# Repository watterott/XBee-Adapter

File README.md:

# XBee-Adapter
The XBee-Adapter is an USB to serial adapter and breakout for XBee modules.

* [FTDI FT231X](https://www.ftdichip.com/Products/ICs/FT231X.html) USB UART Bridge
* 3.3V 0.8A LDO voltage regulator
* Status LEDs
* All pins available on 2.54mm headers
* microUSB-Connector
* Open-Source and released under the [Creative Commons Attribution Share-Alike License](https://creativecommons.org/licenses/by-sa/4.0/).
* **[Documentation on learn.watterott.com](https://learn.watterott.com)**

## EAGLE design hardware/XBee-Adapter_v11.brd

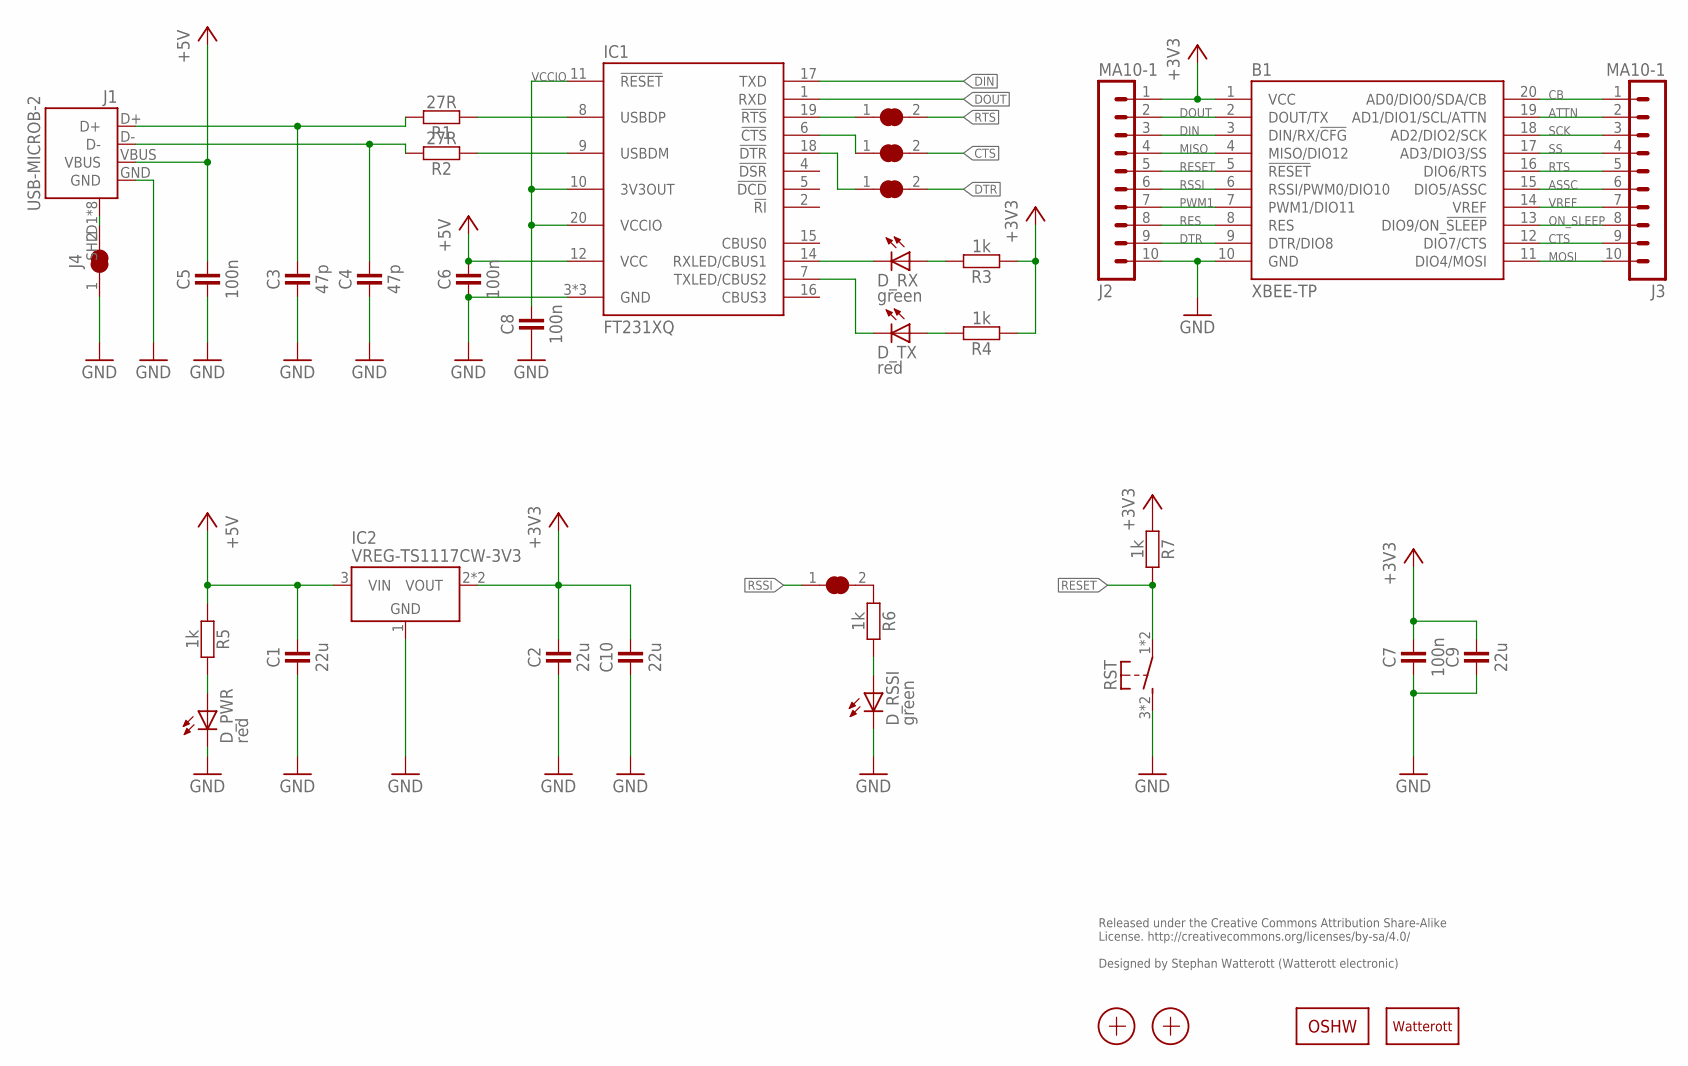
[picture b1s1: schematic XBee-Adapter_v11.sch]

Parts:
B1: XBEE-TP; XBEE_TP
C1, C2, C9, C10: 22u; C0805
C3, C4: 47p; C0402
C5, C6, C7, C8: 100n; C0402
CTS: JUMPER2-0603
DTR: JUMPER2-0603
D_PWR: red; C0603
D_RSSI: green; C0603
D_RX: green; C0603
D_TX: red; C0603
IC1: FT231XQ; QFN20-PAD
IC2: VREG-TS1117CW-3V3; SOT223
J1: USB-MICROB-2; USB-MICROB-10118194
J2, J3: MA10-1
J4: JUMPER2-0603
LOGO1: OSHW_LOGOX0150; OSHW_6X150
LOGO2: LOGO-S_PLACE_M; SPARK_TPLACE_M
R1, R2: 27R; C0603
R3, R4, R5, R6, R7: 1k; C0402
RSSI: JUMPER2-0603
RST: SW-TACTILE-PTS840P; PTS840P
RTS: JUMPER2-0603
X1, X2: PASSER-07; PASSER_07MM

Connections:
+3V3: B1.1 (VCC), C2.2, C7.2, C9.2, C10.2, IC2.2 (VOUT), IC2.4 (VOUT), J2.1, R3.1, R4.1, R7.1
+5V: C1.2, C5.2, C6.2, IC1.12 (VCC), IC2.3 (VIN), J1.VBUS, R5.1
ASSC: B1.15 (DIO5/ASSC), J3.6
ATTN: B1.19 (AD1/DIO1/SCL/ATTN), J3.2
CB: B1.20 (AD0/DIO0/SDA/CB), J3.1
CTS: B1.12 (DIO7/CTS), CTS.2, J3.9
DIN: B1.3 (DIN/RX/!CFG!), IC1.17 (TXD), J2.3
DOUT: B1.2 (DOUT/TX), IC1.1 (RXD), J2.2
DTR: B1.9 (DTR/DIO8), DTR.2, J2.9
D_N: C4.2, J1.D-, R2.2
D_P: C3.2, J1.D+, R1.2
GND: B1.10 (GND), C1.1, C2.1, C3.1, C4.1, C5.1, C6.1, C7.1, C8.1, C9.1, C10.1, D_PWR.C, D_RSSI.C, IC1.3 (GND), IC1.13 (GND), IC1.TP (GND), IC2.1 (GND), J1.GND, J2.10, J4.1, RST.3 (S1), RST.4 (S1)
MISO: B1.4 (MISO/DIO12), J2.4
MOSI: B1.11 (DIO4/MOSI), J3.10
unnamed: D_PWR.A, R5.2
unnamed: D_RSSI.A, R6.2
unnamed: R6.1, RSSI.2
unnamed: J1.SHLD1 (SHIELD), J1.SHLD2 (SHIELD), J1.SHLD3 (SHIELD), J1.SHLD4 (SHIELD), J1.SHLD5 (SHIELD), J1.SHLD6 (SHIELD), J1.SHLD7 (SHIELD), J1.SHLD8 (SHIELD), J4.2
unnamed: IC1.19 (!RTS), RTS.1
unnamed: CTS.1, IC1.6 (!CTS)
unnamed: D_RX.C, IC1.14 (RXLED/CBUS1)
unnamed: D_TX.C, IC1.7 (TXLED/CBUS2)
unnamed: D_RX.A, R3.2
unnamed: D_TX.A, R4.2
unnamed: DTR.1, IC1.18 (!DTR)
ON_SLEEP: B1.13 (DIO9/ON_!SLEEP!), J3.8
PWM1: B1.7 (PWM1/DIO11), J2.7
RES: B1.8 (RES), J2.8
RESET: B1.5 (!RESET!), J2.5, R7.2, RST.1, RST.2 (P1)
RSSI: B1.6 (RSSI/PWM0/DIO10), J2.6, RSSI.1
RTS: B1.16 (DIO6/RTS), J3.5, RTS.2
SCK: B1.18 (AD2/DIO2/SCK), J3.3
SS: B1.17 (AD3/DIO3/SS), J3.4
USB_N: IC1.9 (USBDM), R2.1
USB_P: IC1.8 (USBDP), R1.1
VCCIO: C8.2, IC1.10 (3V3OUT), IC1.11 (!RESET), IC1.20 (VCCIO)
VREF: B1.14 (VREF), J3.7

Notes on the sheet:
Released under the Creative Commons Attribution Share-Alike License. http://creativecommons.org/licenses/by-sa/4.0/ Designed by Stephan Watterott (Watterott electronic)

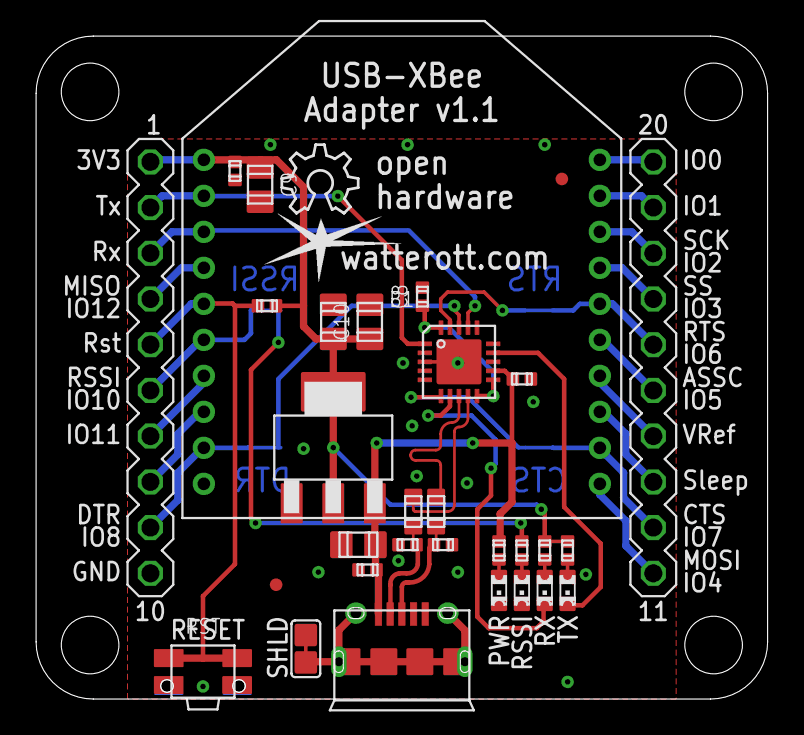
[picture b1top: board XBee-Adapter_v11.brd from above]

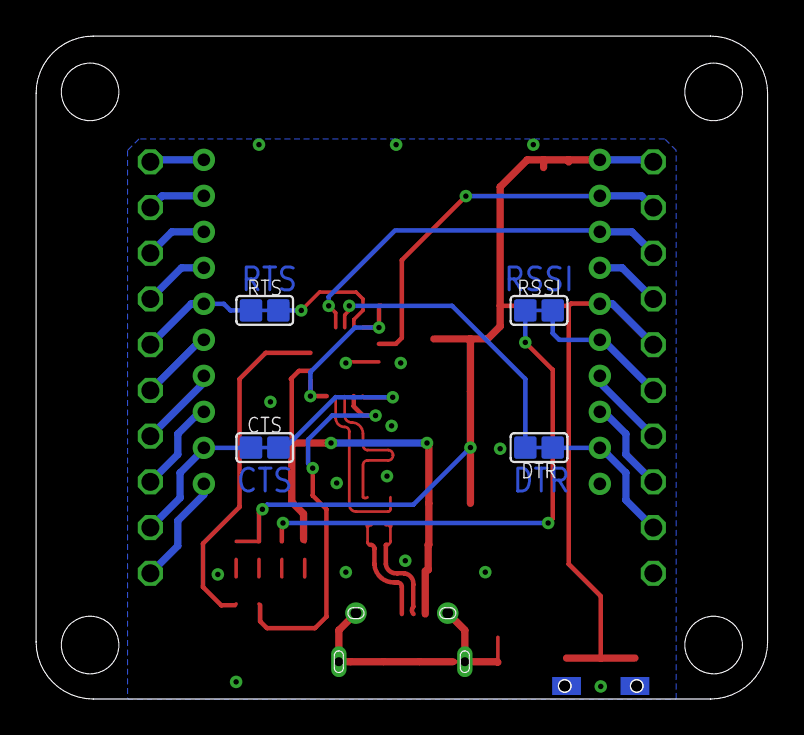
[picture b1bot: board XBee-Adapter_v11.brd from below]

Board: 2 copper layers, 40.6 x 36.8 mm, 37 parts (4 on the bottom side), 37 nets.

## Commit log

2017-07-30 updted readme
2017-10-25 added rev 1.2
